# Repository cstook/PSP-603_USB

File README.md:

# PSP-603_USB
circuit to convert PSP-603 from RS-232 to USB

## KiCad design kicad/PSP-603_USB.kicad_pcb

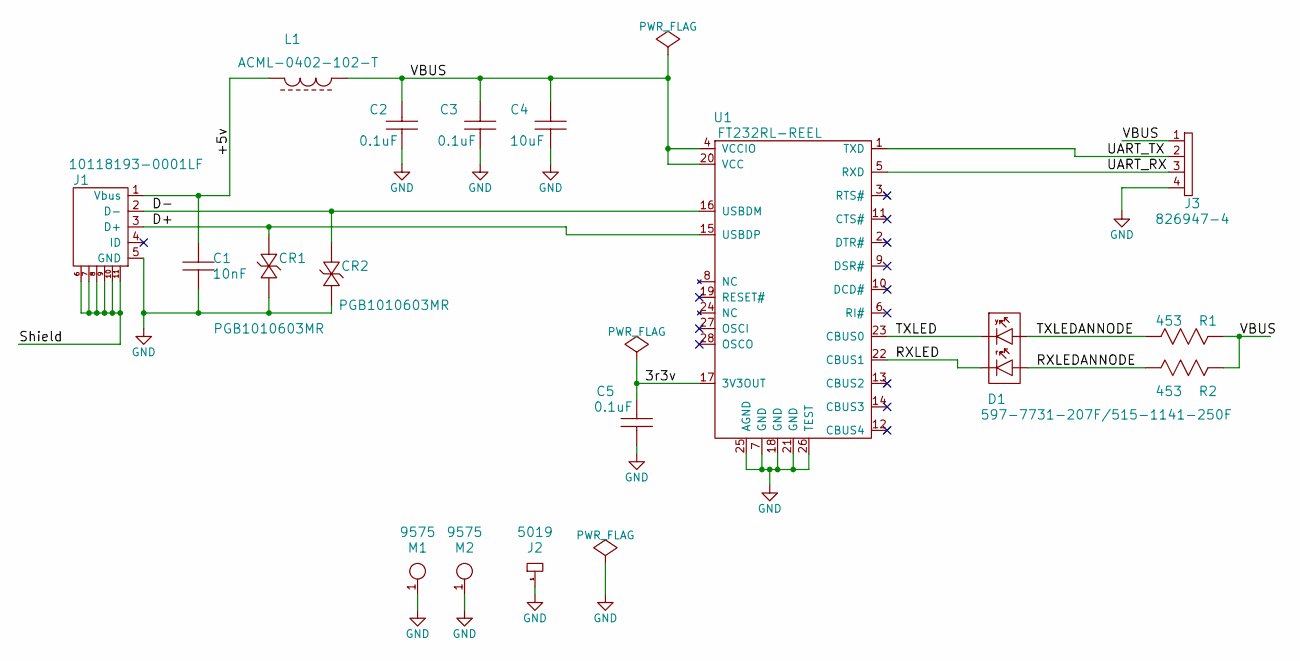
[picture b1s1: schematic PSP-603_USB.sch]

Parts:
C1: C0603C103J2RACTU; C0603; Voltage 200V; Tolerance +/- 5%; mfg part number C0603C103J2RACTU
C2, C3, C5: C1005X7R1H104K050BB; C0402; Voltage 50V; Tolerance +/- 10%; mfg part number C1005X7R1H104K050BB
C4: EMK212BB7106MG-T; C0805; Voltage 16V; Tolerance +/-20%; mfg part number EMK212BB7106MG-T
CR1, CR2: PGB1010603MR; PGB1_01_0603; mft part number PGB1010603MR
D1: 597-7731-207F/515-1141-250F; PLCC-4_515-114; Forward Voltage 2.0V typ.; mfg part number 597-7731-207F
J1: 10118193-0001LF; mfg part number 10118193-0001LF
J2: 5019; 5090; mfg part number 5019
J3: 826947-4; mfg part number 826947-4
L1: ACML-0402-102-T; C0402; mfg part number ACML-0402-102-T
M1, M2: 9575; mfg part number 9575
R1, R2: CRCW0805453RFKEA; R0805; Tolerance 1%; mfg part number CRCW0805453RFKEA
U1: FT232RL-REEL; SSOP-28; mfg part number FT232RL-REEL

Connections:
/3r3v: C5.2, U1.17 (3V3OUT)
/+5v: C1.2, J1.1 (Vbus), L1.2
/D+: CR1.1, J1.3 (D+), U1.15 (USBDP)
/D-: CR2.1, J1.2 (D-), U1.16 (USBDM)
/RXLED: D1.1 (RC), U1.22 (CBUS1)
/RXLEDANNODE: D1.2 (RA), R2.1
/Shield: J1.6, J1.7, J1.8, J1.9, J1.10, J1.11
/TXLED: D1.3 (YC), U1.23 (CBUS0)
/TXLEDANNODE: D1.4 (YA), R1.1
/UART_RX: J3.3, U1.5 (RXD)
/UART_TX: J3.2, U1.1 (TXD)
/VBUS: C2.2, C3.2, C4.2, J3.1, L1.1, R1.2, R2.2, U1.4 (VCCIO), U1.20 (VCC)
GND: C1.1, C2.1, C3.1, C4.1, C5.1, CR1.2, CR2.2, J1.5 (GND), J2.1, J3.4, M1.1, M2.1, U1.7 (GND), U1.18 (GND), U1.21 (GND), U1.25 (AGND), U1.26 (TEST)

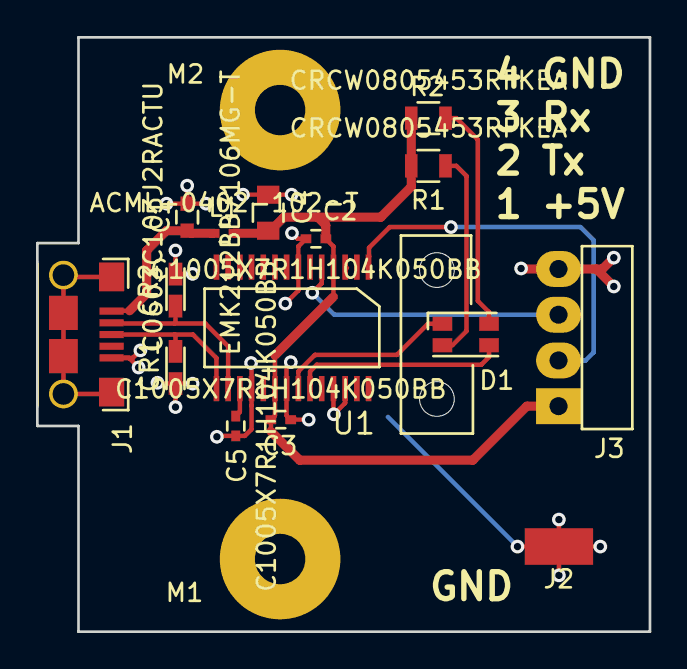
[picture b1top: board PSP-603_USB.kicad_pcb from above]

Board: 2 copper layers, 34.0 x 33.0 mm, 17 parts (0 on the bottom side), 13 nets.

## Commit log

2016-03-25 Polarity is backwards. This is the last commit before switching to FT232R Also, added config file for FT232H
2016-03-26 Switched to FT232R
2016-03-26 redo layout Signed-off-by: Chris Stook <chris@chrisstook.com>
2016-04-23 tied test pin to gnd.
